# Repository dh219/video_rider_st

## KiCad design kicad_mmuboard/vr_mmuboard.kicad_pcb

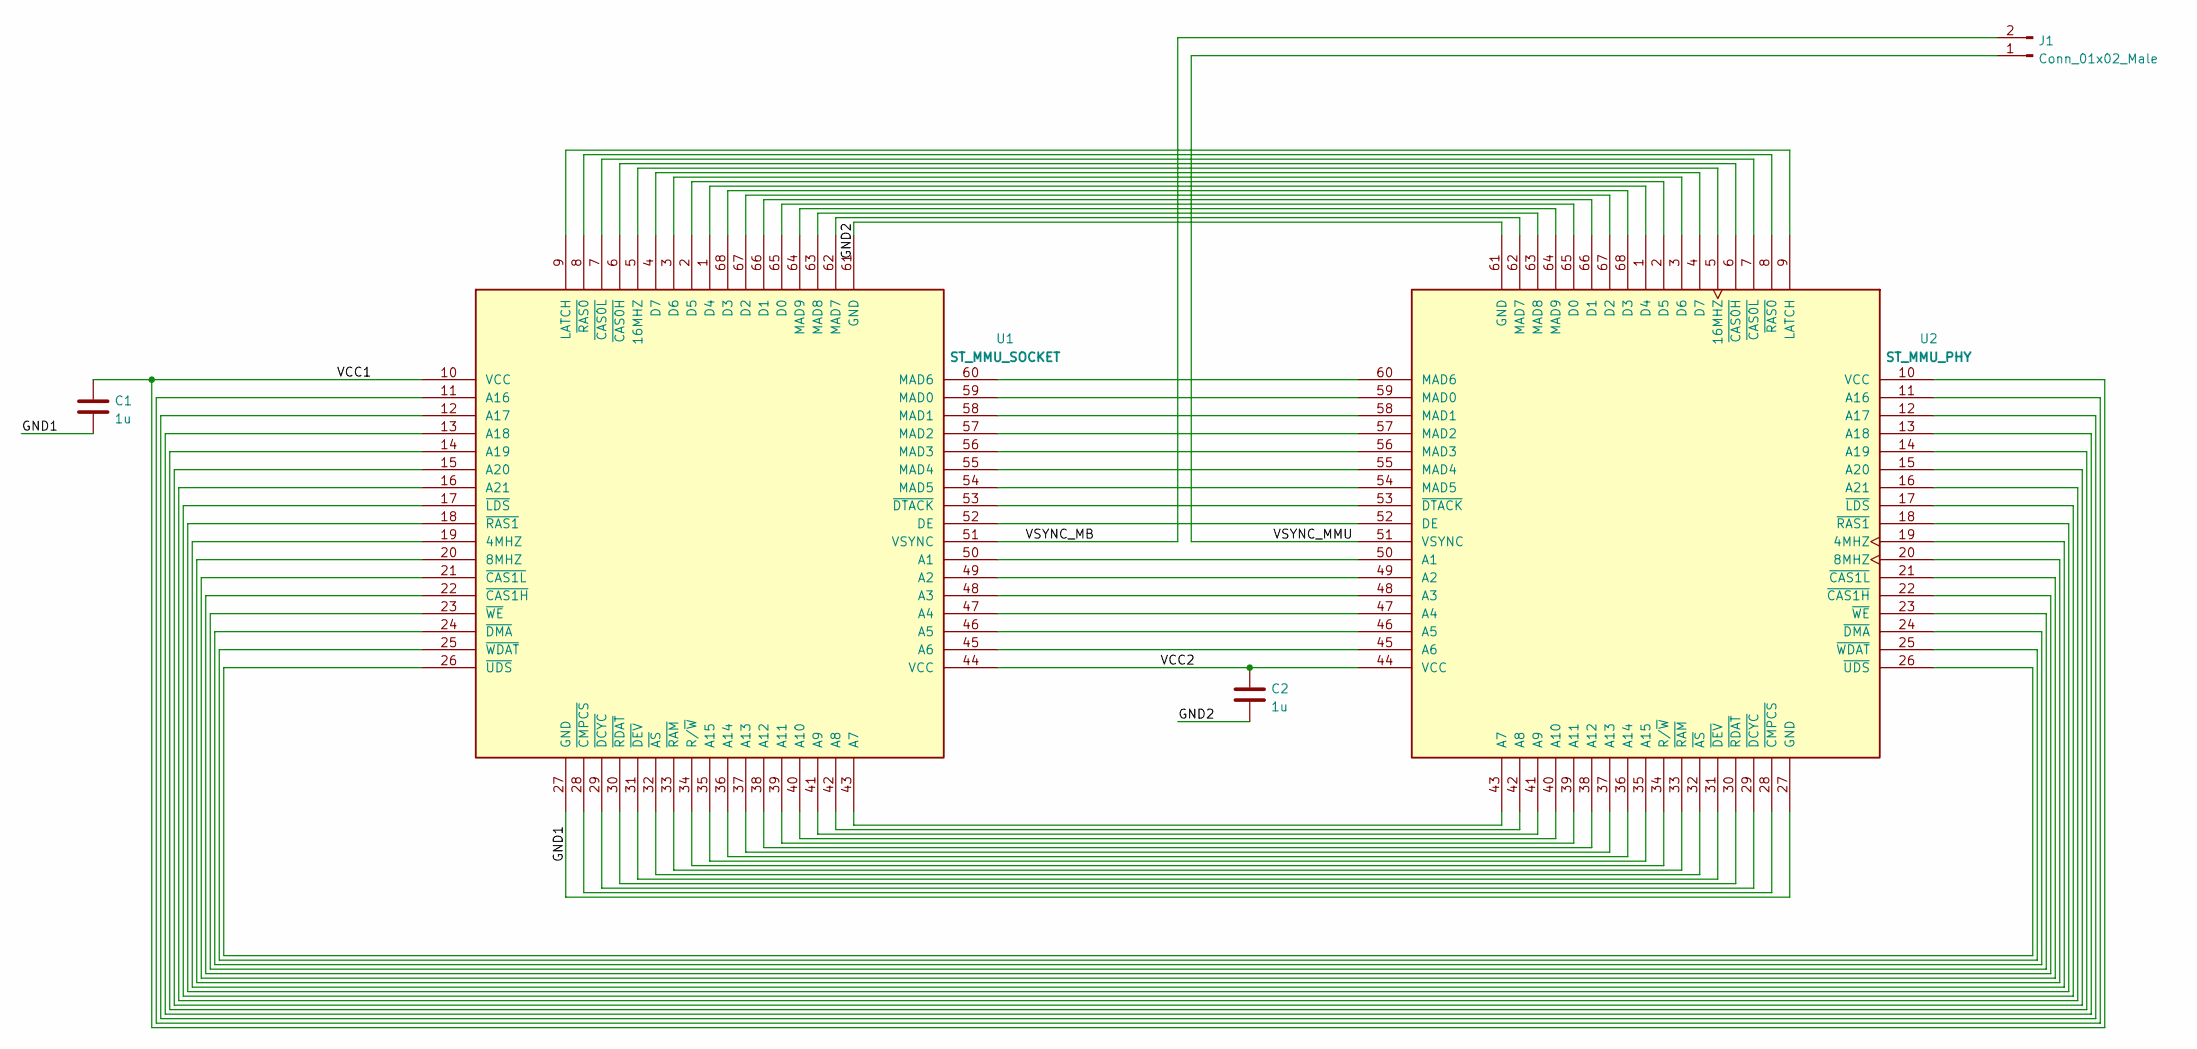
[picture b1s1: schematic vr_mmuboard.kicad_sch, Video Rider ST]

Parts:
C1, C2: 1u; C_0805_2012Metric_Pad1.18x1.45mm_HandSolder
J1: Conn_01x02_Male; PinHeader_1x02_P2.54mm_Horizontal
U1: ST_MMU_SOCKET; PLCC68_male_pins
U2: ST_MMU_PHY; PLCC-68_THT-Socket

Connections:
/GND1: C1.2, U1.27 (GND), U2.27 (GND)
/GND2: C2.2, U1.61 (GND), U2.61 (GND)
/VCC1: C1.1, U1.10 (VCC), U2.10 (VCC)
/VCC2: C2.1, U1.44 (VCC), U2.44 (VCC)
/VSYNC_MB: J1.2, U1.51 (VSYNC)
/VSYNC_MMU: J1.1, U2.51 (VSYNC)
unnamed: U1.1 (D4), U2.1 (D4)
unnamed: U1.2 (D5), U2.2 (D5)
unnamed: U1.3 (D6), U2.3 (D6)
unnamed: U1.4 (D7), U2.4 (D7)
unnamed: U1.5 (16MHZ), U2.5 (16MHZ)
unnamed: U1.6 (~CAS0H), U2.6 (~CAS0H)
unnamed: U1.7 (~CAS0L), U2.7 (~CAS0L)
unnamed: U1.8 (~RAS0), U2.8 (~RAS0)
unnamed: U1.9 (LATCH), U2.9 (LATCH)
unnamed: U1.11 (A16), U2.11 (A16)
unnamed: U1.12 (A17), U2.12 (A17)
unnamed: U1.13 (A18), U2.13 (A18)
unnamed: U1.14 (A19), U2.14 (A19)
unnamed: U1.15 (A20), U2.15 (A20)
unnamed: U1.16 (A21), U2.16 (A21)
unnamed: U1.17 (~LDS), U2.17 (~LDS)
unnamed: U1.18 (~RAS1), U2.18 (~RAS1)
unnamed: U1.19 (4MHZ), U2.19 (4MHZ)
unnamed: U1.20 (8MHZ), U2.20 (8MHZ)
unnamed: U1.21 (~CAS1L), U2.21 (~CAS1L)
unnamed: U1.22 (~CAS1H), U2.22 (~CAS1H)
unnamed: U1.23 (~WE), U2.23 (~WE)
unnamed: U1.24 (~DMA), U2.24 (~DMA)
unnamed: U1.25 (~WDAT), U2.25 (~WDAT)
unnamed: U1.26 (~UDS), U2.26 (~UDS)
unnamed: U1.28 (~CMPCS), U2.28 (~CMPCS)
unnamed: U1.29 (~DCYC), U2.29 (~DCYC)
unnamed: U1.30 (~RDAT), U2.30 (~RDAT)
unnamed: U1.31 (~DEV), U2.31 (~DEV)
unnamed: U1.32 (~AS), U2.32 (~AS)
unnamed: U1.33 (~RAM), U2.33 (~RAM)
unnamed: U1.34 (R/~W), U2.34 (R/~W)
unnamed: U1.35 (A15), U2.35 (A15)
unnamed: U1.36 (A14), U2.36 (A14)
unnamed: U1.37 (A13), U2.37 (A13)
unnamed: U1.38 (A12), U2.38 (A12)
unnamed: U1.39 (A11), U2.39 (A11)
unnamed: U1.40 (A10), U2.40 (A10)
unnamed: U1.41 (A9), U2.41 (A9)
unnamed: U1.42 (A8), U2.42 (A8)
unnamed: U1.43 (A7), U2.43 (A7)
unnamed: U1.45 (A6), U2.45 (A6)
unnamed: U1.46 (A5), U2.46 (A5)
unnamed: U1.47 (A4), U2.47 (A4)
unnamed: U1.48 (A3), U2.48 (A3)
unnamed: U1.49 (A2), U2.49 (A2)
unnamed: U1.50 (A1), U2.50 (A1)
unnamed: U1.52 (DE), U2.52 (DE)
unnamed: U1.53 (~DTACK), U2.53 (~DTACK)
unnamed: U1.54 (MAD5), U2.54 (MAD5)
unnamed: U1.55 (MAD4), U2.55 (MAD4)
unnamed: U1.56 (MAD3), U2.56 (MAD3)
unnamed: U1.57 (MAD2), U2.57 (MAD2)
unnamed: U1.58 (MAD1), U2.58 (MAD1)
unnamed: U1.59 (MAD0), U2.59 (MAD0)
unnamed: U1.60 (MAD6), U2.60 (MAD6)
unnamed: U1.62 (MAD7), U2.62 (MAD7)
unnamed: U1.63 (MAD8), U2.63 (MAD8)
unnamed: U1.64 (MAD9), U2.64 (MAD9)
unnamed: U1.65 (D0), U2.65 (D0)
unnamed: U1.66 (D1), U2.66 (D1)
unnamed: U1.67 (D2), U2.67 (D2)
unnamed: U1.68 (D3), U2.68 (D3)

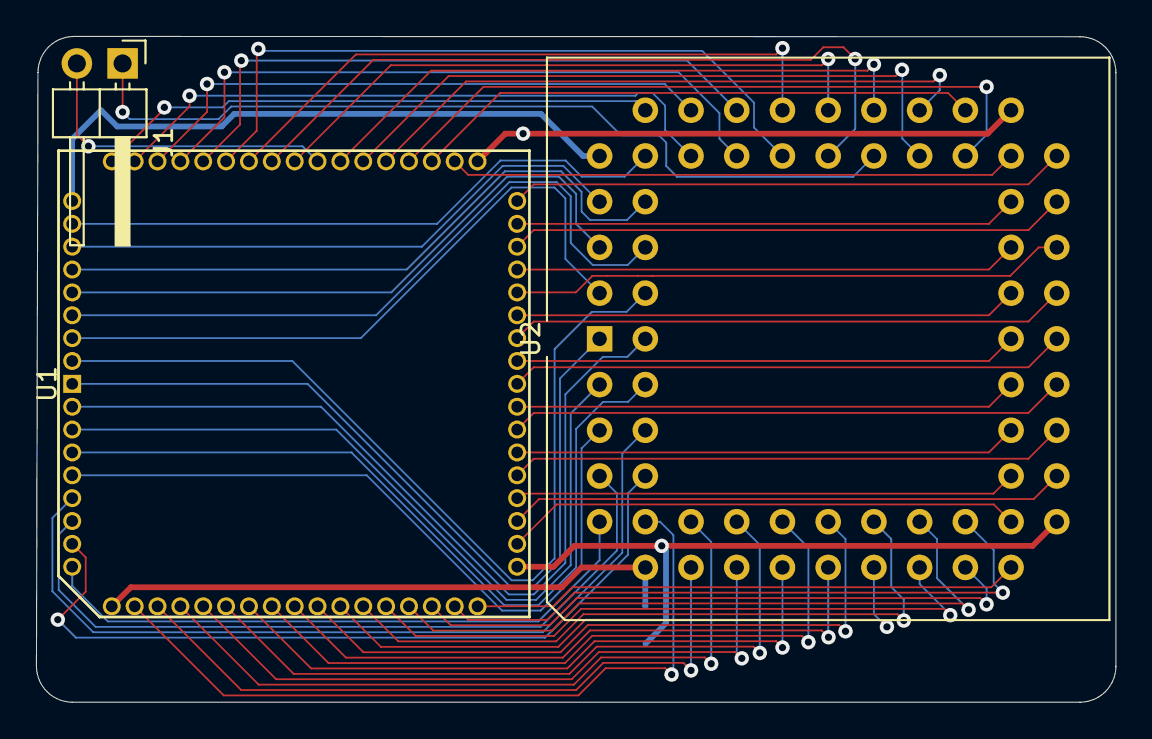
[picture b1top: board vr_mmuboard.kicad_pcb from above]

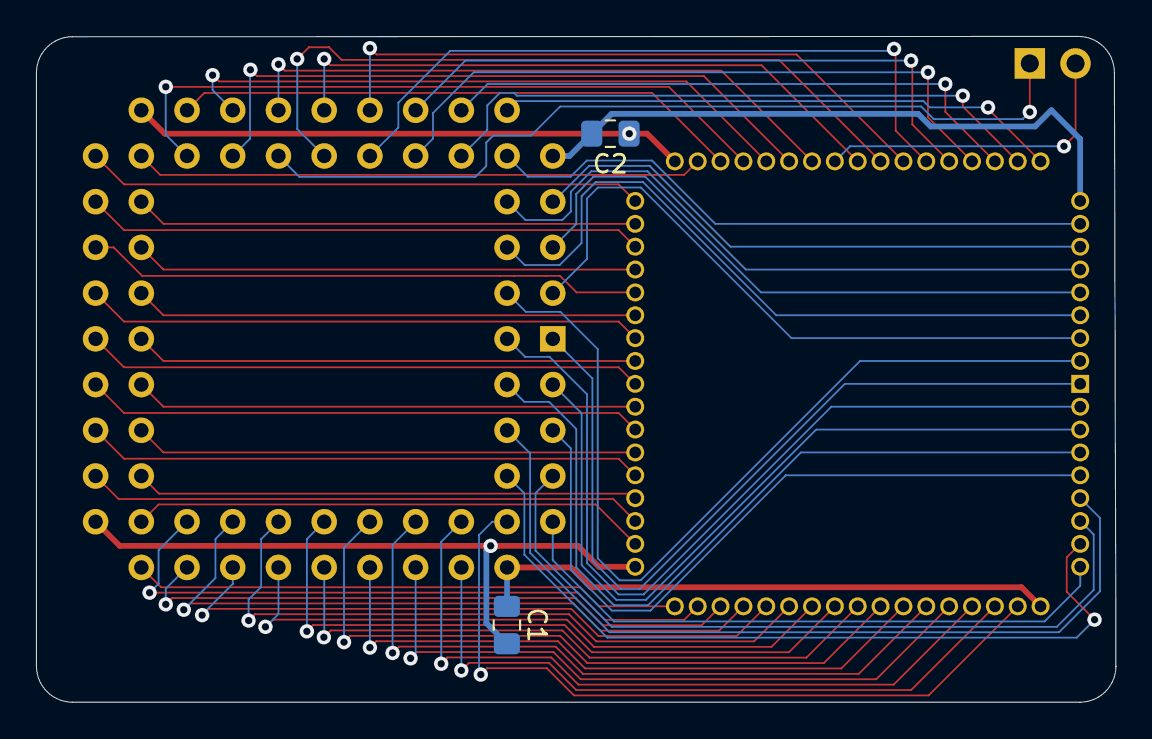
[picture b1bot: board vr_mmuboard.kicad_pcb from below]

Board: 2 copper layers, 60.0 x 37.0 mm, 5 parts (2 on the bottom side), 69 nets.

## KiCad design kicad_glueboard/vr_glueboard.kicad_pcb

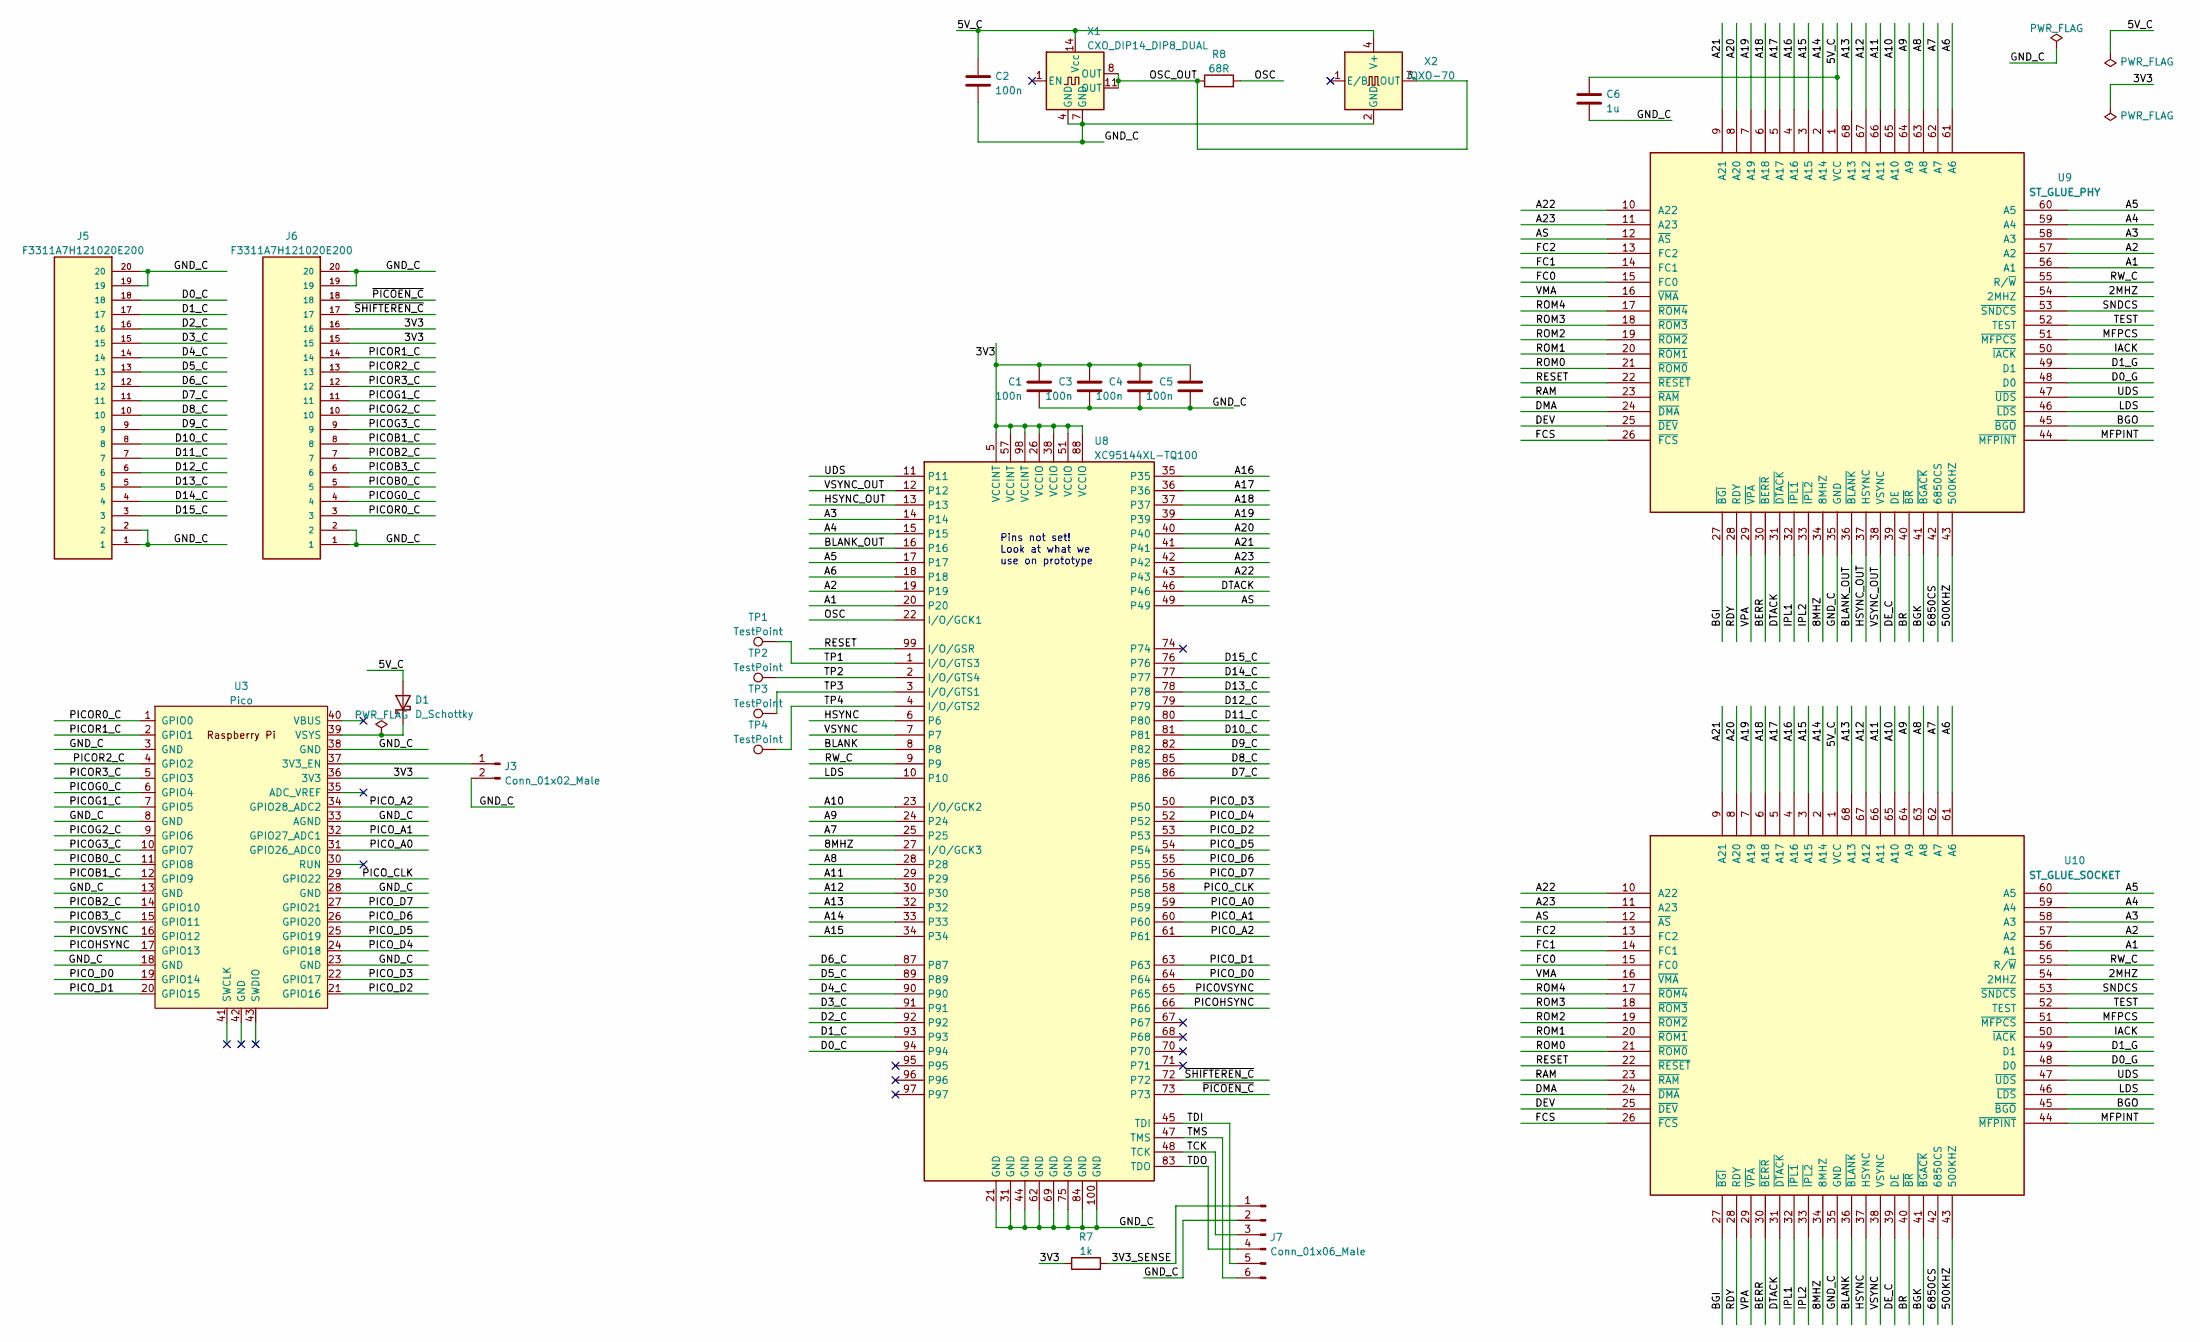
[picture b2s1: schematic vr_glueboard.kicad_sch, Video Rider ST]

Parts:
C1, C2, C3, C4, C5: 100n; C_0805_2012Metric_Pad1.18x1.45mm_HandSolder
C6: 1u; C_0805_2012Metric_Pad1.18x1.45mm_HandSolder
D1: D_Schottky; D_0805_2012Metric_Pad1.15x1.40mm_HandSolder
J3: Conn_01x02_Male; PinHeader_1x02_P2.54mm_Vertical
J5, J6: F3311A7H121020E200; AMPHENOL_F3311A7H121020E200; PARTREV A
J7: Conn_01x06_Male; PinHeader_1x06_P2.54mm_Vertical
R7: 1k; R_0805_2012Metric_Pad1.20x1.40mm_HandSolder
R8: 68R; R_0805_2012Metric_Pad1.20x1.40mm_HandSolder
TP1, TP2, TP3, TP4: TestPoint; TestPoint_THTPad_1.5x1.5mm_Drill0.7mm
U3: Pico; RPi_Pico_SMD_TH
U8: XC95144XL-TQ100; TQFP-100_14x14mm_P0.5mm
U9: ST_GLUE_PHY; PLCC68_male_pins
U10: ST_GLUE_SOCKET; PLCC-68_THT-Socket
X1: CXO_DIP14_DIP8_DUAL; CXO_Dual_DIP
X2: IQXO-70; Oscillator_SMD_IQD_IQXO70-4Pin_7.5x5.0mm

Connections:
/2MHZ: U9.54 (2MHZ), U10.54 (2MHZ)
/3V3: C1.1, C3.1, C4.1, C5.1, J6.15, J6.16, R7.1, U3.36 (3V3), U8.5 (VCCINT), U8.26 (VCCIO), U8.38 (VCCIO), U8.51 (VCCIO), U8.57 (VCCINT), U8.88 (VCCIO), U8.98 (VCCINT)
/3V3_SENSE: J7.1, R7.2
/5V_C: C2.1, C6.1, D1.2 (A), U9.1 (VCC), U10.1 (VCC), X1.14 (Vcc), X2.4 (V+)
/8MHZ: U8.27 (I/O/GCK3), U9.34 (8MHZ), U10.34 (8MHZ)
/500KHZ: U9.43 (500KHZ), U10.43 (500KHZ)
/6850CS: U9.42 (6850CS), U10.42 (6850CS)
/A1: U8.20, U9.56 (A1), U10.56 (A1)
/A2: U8.19, U9.57 (A2), U10.57 (A2)
/A3: U8.14, U9.58 (A3), U10.58 (A3)
/A4: U8.15, U9.59 (A4), U10.59 (A4)
/A5: U8.17, U9.60 (A5), U10.60 (A5)
/A6: U8.18, U9.61 (A6), U10.61 (A6)
/A7: U8.25, U9.62 (A7), U10.62 (A7)
/A8: U8.28, U9.63 (A8), U10.63 (A8)
/A9: U8.24, U9.64 (A9), U10.64 (A9)
/A10: U8.23 (I/O/GCK2), U9.65 (A10), U10.65 (A10)
/A11: U8.29, U9.66 (A11), U10.66 (A11)
/A12: U8.30, U9.67 (A12), U10.67 (A12)
/A13: U8.32, U9.68 (A13), U10.68 (A13)
/A14: U8.33, U9.2 (A14), U10.2 (A14)
/A15: U8.34, U9.3 (A15), U10.3 (A15)
/A16: U8.35, U9.4 (A16), U10.4 (A16)
/A17: U8.36, U9.5 (A17), U10.5 (A17)
/A18: U8.37, U9.6 (A18), U10.6 (A18)
/A19: U8.39, U9.7 (A19), U10.7 (A19)
/A20: U8.40, U9.8 (A20), U10.8 (A20)
/A21: U8.41, U9.9 (A21), U10.9 (A21)
/A22: U8.43, U9.10 (A22), U10.10 (A22)
/A23: U8.42, U9.11 (A23), U10.11 (A23)
/AS: U8.49, U9.12 (~AS), U10.12 (~AS)
/BERR: U9.30 (~BERR), U10.30 (~BERR)
/BGI: U9.27 (~BGI), U10.27 (~BGI)
/BGK: U9.41 (~BGACK), U10.41 (~BGACK)
/BGO: U9.45 (~BGO), U10.45 (~BGO)
/BLANK: U8.8, U10.36 (~BLANK)
/BLANK_OUT: U8.16, U9.36 (~BLANK)
/BR: U9.40 (~BR), U10.40 (~BR)
/D0_C: J5.18, U8.94
/D0_G: U9.48 (D0), U10.48 (D0)
/D1_C: J5.17, U8.93
/D1_G: U9.49 (D1), U10.49 (D1)
/D2_C: J5.16, U8.92
/D3_C: J5.15, U8.91
/D4_C: J5.14, U8.90
/D5_C: J5.13, U8.89
/D6_C: J5.12, U8.87
/D7_C: J5.11, U8.86
/D8_C: J5.10, U8.85
/D9_C: J5.9, U8.82
/D10_C: J5.8, U8.81
/D11_C: J5.7, U8.80
/D12_C: J5.6, U8.79
/D13_C: J5.5, U8.78
/D14_C: J5.4, U8.77
/D15_C: J5.3, U8.76
/DEV: U9.25 (~DEV), U10.25 (~DEV)
/DE_C: U9.39 (DE), U10.39 (DE)
/DMA: U9.24 (~DMA), U10.24 (~DMA)
/DTACK: U8.46, U9.31 (~DTACK), U10.31 (~DTACK)
/FC0: U9.15 (FC0), U10.15 (FC0)
/FC1: U9.14 (FC1), U10.14 (FC1)
/FC2: U9.13 (FC2), U10.13 (FC2)
/FCS: U9.26 (~FCS), U10.26 (~FCS)
/GND_C: C1.2, C2.2, C3.2, C4.2, C5.2, C6.2, J3.2, J5.1, J5.2, J5.19, J5.20, J5.SH1, J5.SH2, J6.1, J6.2, J6.19, J6.20, J6.SH1, J6.SH2, J7.2, U3.3 (GND), U3.8 (GND), U3.13 (GND), U3.18 (GND), U3.23 (GND), U3.28 (GND), U3.33 (AGND), U3.38 (GND), U8.21 (GND), U8.31 (GND), U8.44 (GND), U8.62 (GND), U8.69 (GND), U8.75 (GND), U8.84 (GND), U8.100 (GND), U9.35 (GND), U10.35 (GND), X1.4 (GND), X1.7 (GND), X2.2 (GND)
/HSYNC: U8.6, U10.37 (HSYNC)
/HSYNC_OUT: U8.13, U9.37 (HSYNC)
/IACK: U9.50 (~IACK), U10.50 (~IACK)
/IPL1: U9.32 (~IPL1), U10.32 (~IPL1)
/IPL2: U9.33 (~IPL2), U10.33 (~IPL2)
/LDS: U8.10, U9.46 (~LDS), U10.46 (~LDS)
/MFPCS: U9.51 (~MFPCS), U10.51 (~MFPCS)
/MFPINT: U9.44 (~MFPINT), U10.44 (~MFPINT)
/OSC: R8.2, U8.22 (I/O/GCK1)
/OSC_OUT: R8.1, X1.8 (OUT), X1.11 (OUT), X2.3 (OUT)
/PICOB0_C: J6.5, U3.11 (GPIO8)
/PICOB1_C: J6.8, U3.12 (GPIO9)
/PICOB2_C: J6.7, U3.14 (GPIO10)
/PICOB3_C: J6.6, U3.15 (GPIO11)
/PICOG0_C: J6.4, U3.6 (GPIO4)
/PICOG1_C: J6.11, U3.7 (GPIO5)
/PICOG2_C: J6.10, U3.9 (GPIO6)
/PICOG3_C: J6.9, U3.10 (GPIO7)
/PICOHSYNC: U3.17 (GPIO13), U8.66
/PICOR0_C: J6.3, U3.1 (GPIO0)
/PICOR1_C: J6.14, U3.2 (GPIO1)
/PICOR2_C: J6.13, U3.4 (GPIO2)
/PICOR3_C: J6.12, U3.5 (GPIO3)
/PICOVSYNC: U3.16 (GPIO12), U8.65
/PICO_A0: U3.31 (GPIO26_ADC0), U8.59
/PICO_A1: U3.32 (GPIO27_ADC1), U8.60
/PICO_A2: U3.34 (GPIO28_ADC2), U8.61
/PICO_CLK: U3.29 (GPIO22), U8.58
/PICO_D0: U3.19 (GPIO14), U8.64
/PICO_D1: U3.20 (GPIO15), U8.63
/PICO_D2: U3.21 (GPIO16), U8.53
/PICO_D3: U3.22 (GPIO17), U8.50
/PICO_D4: U3.24 (GPIO18), U8.52
/PICO_D5: U3.25 (GPIO19), U8.54
/PICO_D6: U3.26 (GPIO20), U8.55
/PICO_D7: U3.27 (GPIO21), U8.56
/RAM: U9.23 (~RAM), U10.23 (~RAM)
/RDY: U9.28 (RDY), U10.28 (RDY)
/RESET: U8.99 (I/O/GSR), U9.22 (~RESET), U10.22 (~RESET)
/ROM0: U9.21 (~ROM0), U10.21 (~ROM0)
/ROM1: U9.20 (~ROM1), U10.20 (~ROM1)
/ROM2: U9.19 (~ROM2), U10.19 (~ROM2)
/ROM3: U9.18 (~ROM3), U10.18 (~ROM3)
/ROM4: U9.17 (~ROM4), U10.17 (~ROM4)
/RW_C: U8.9, U9.55 (R/~W), U10.55 (R/~W)
/SNDCS: U9.53 (~SNDCS), U10.53 (~SNDCS)
/TCK: J7.3, U8.48 (TCK)
/TDI: J7.5, U8.45 (TDI)
/TDO: J7.4, U8.83 (TDO)
/TEST: U9.52 (TEST), U10.52 (TEST)
/TMS: J7.6, U8.47 (TMS)
/TP1: TP1.1, U8.1 (I/O/GTS3)
/TP2: TP2.1, U8.2 (I/O/GTS4)
/TP3: TP3.1, U8.3 (I/O/GTS1)
/TP4: TP4.1, U8.4 (I/O/GTS2)
/UDS: U8.11, U9.47 (~UDS), U10.47 (~UDS)
/VMA: U9.16 (~VMA), U10.16 (~VMA)
/VPA: U9.29 (~VPA), U10.29 (~VPA)
/VSYNC: U8.7, U10.38 (VSYNC)
/VSYNC_OUT: U8.12, U9.38 (VSYNC)
/~PICOEN_C: J6.18, U8.73
/~SHIFTEREN_C: J6.17, U8.72
unnamed: D1.1 (K), U3.39 (VSYS)
unnamed: J3.1, U3.37 (3V3_EN)

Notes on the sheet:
Pins not set! Look at what we use on prototype

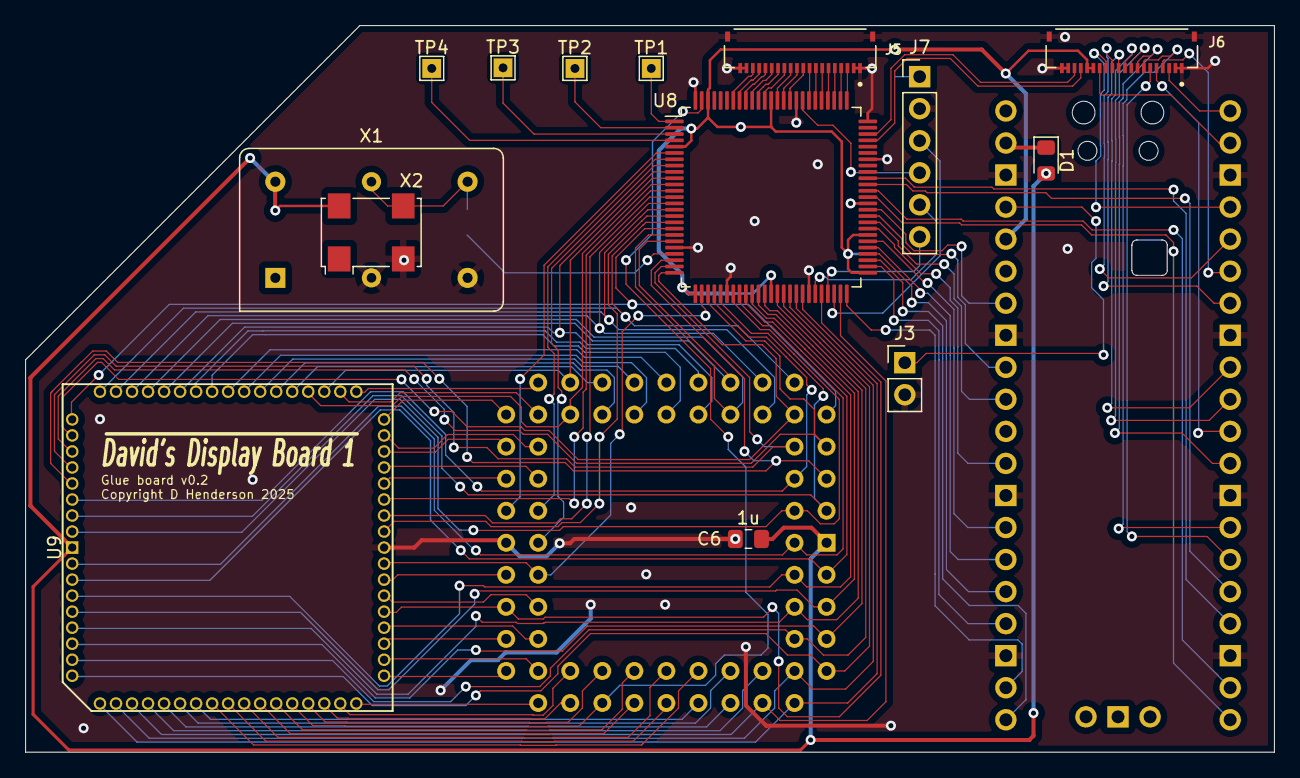
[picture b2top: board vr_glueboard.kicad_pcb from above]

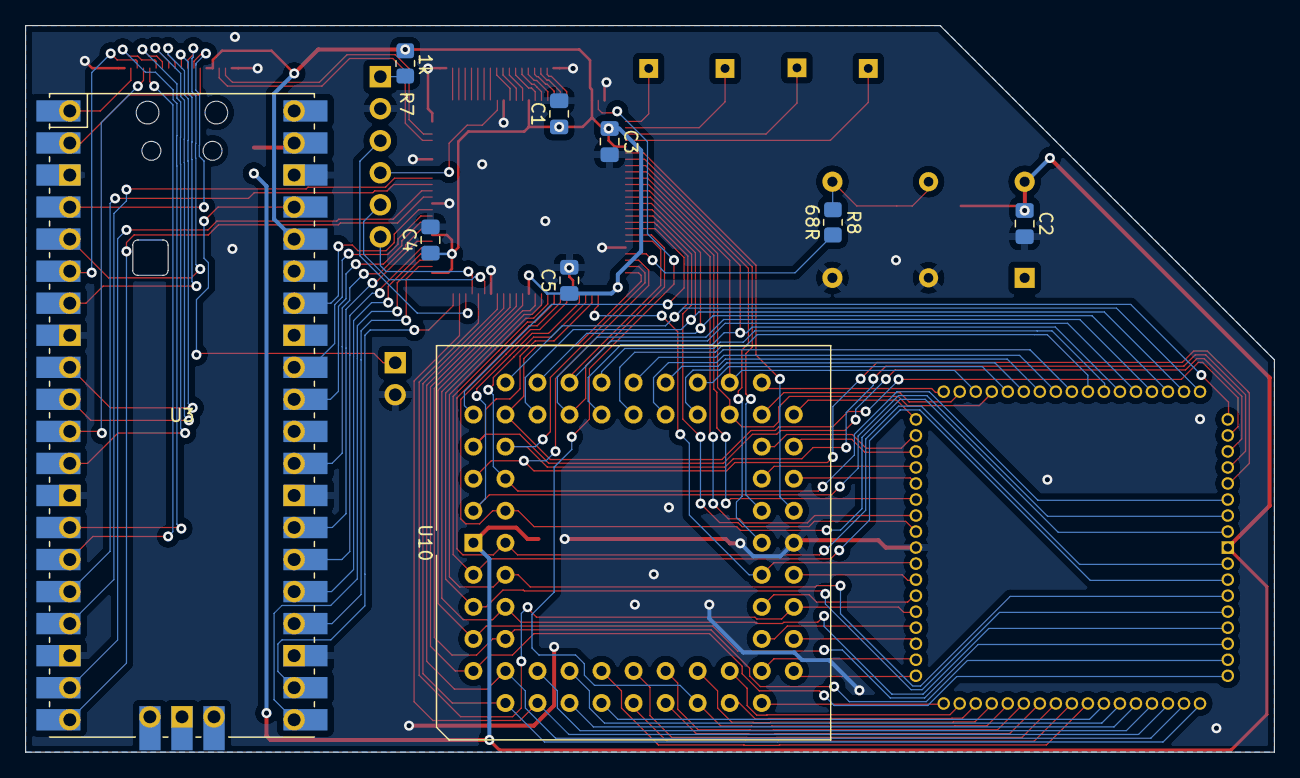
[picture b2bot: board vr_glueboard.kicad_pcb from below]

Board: 2 copper layers, 99.0 x 57.6 mm, 23 parts (9 on the bottom side), 129 nets.

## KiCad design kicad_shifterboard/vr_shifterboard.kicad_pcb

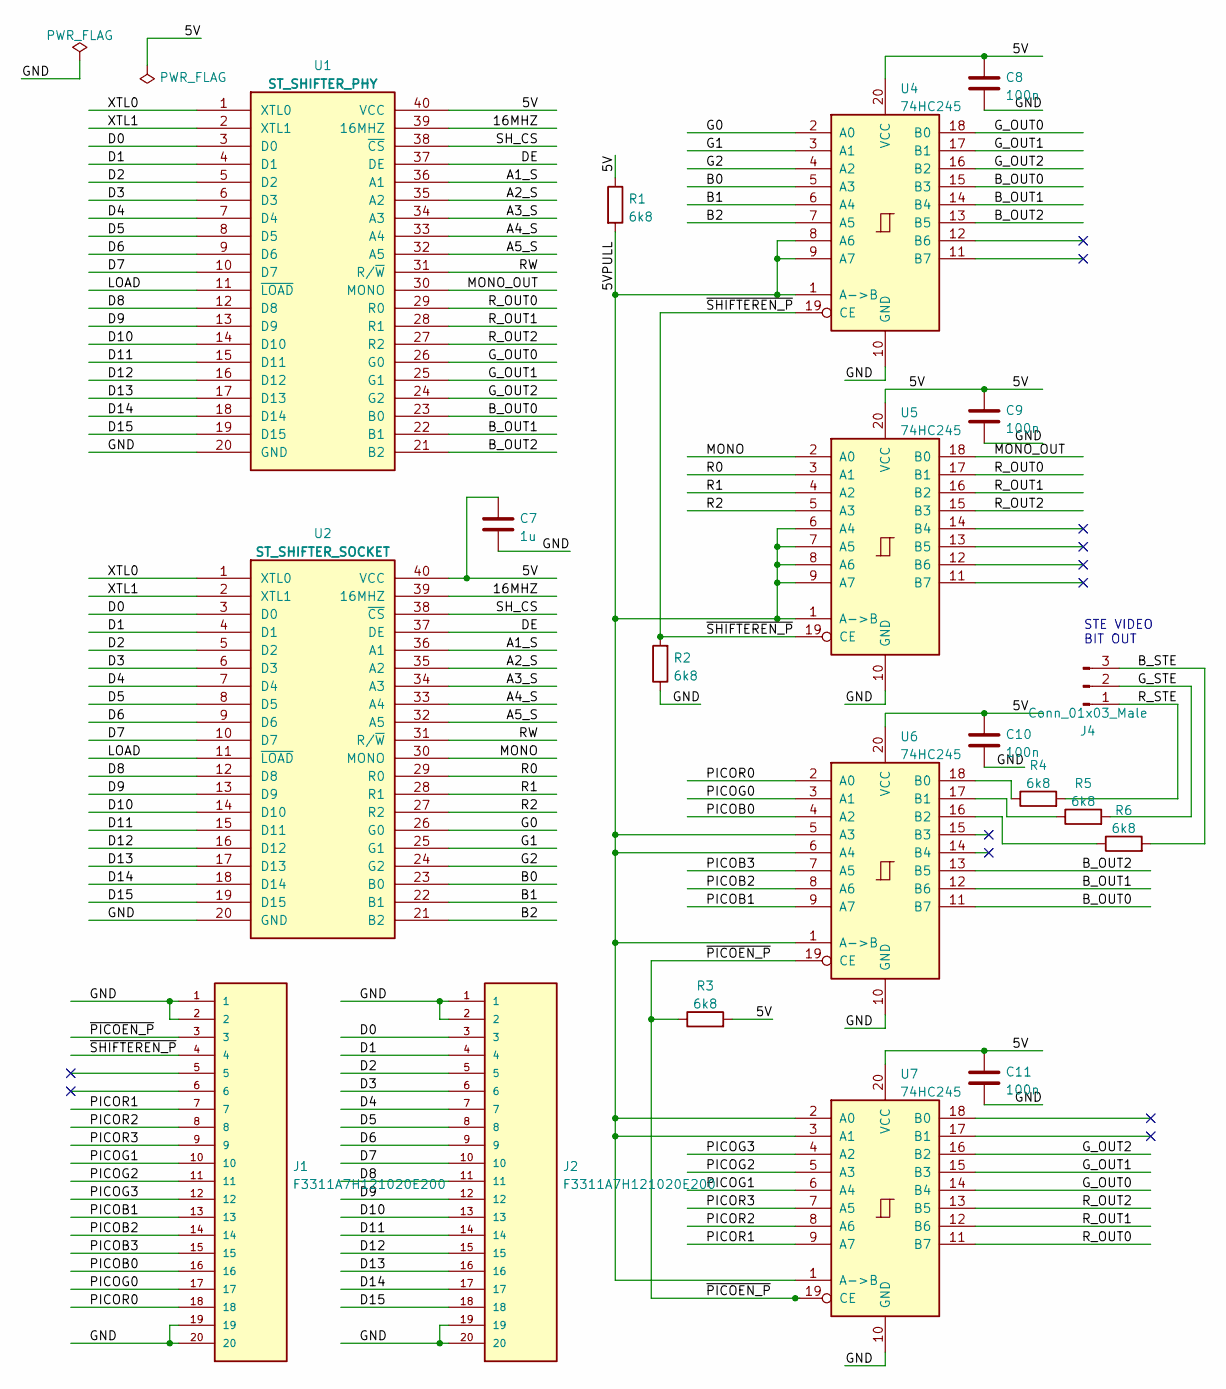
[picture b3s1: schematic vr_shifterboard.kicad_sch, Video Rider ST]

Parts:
C7: 1u; C_0805_2012Metric_Pad1.18x1.45mm_HandSolder
C8, C9, C10, C11: 100n; C_0805_2012Metric_Pad1.18x1.45mm_HandSolder
J1, J2: F3311A7H121020E200; AMPHENOL_F3311A7H121020E200; PARTREV A
J4: Conn_01x03_Male; PinHeader_1x03_P2.54mm_Vertical
R1, R2, R3, R4, R5, R6: 6k8; R_0805_2012Metric_Pad1.20x1.40mm_HandSolder
U1: ST_SHIFTER_PHY; DIP-40_W15.24mm_LongPads
U2: ST_SHIFTER_SOCKET; DIP-40_W15.24mm_LongPads
U4, U5, U6, U7: 74HC245; TSSOP-20_4.4x6.5mm_P0.65mm

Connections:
/5V: C7.1, C8.1, C9.1, C10.1, C11.1, R1.1, R3.2, U1.40 (VCC), U2.40 (VCC), U4.20 (VCC), U5.20 (VCC), U6.20 (VCC), U7.20 (VCC)
/5VPULL: R1.2, U4.1 (A->B), U4.8 (A6), U4.9 (A7), U5.1 (A->B), U5.6 (A4), U5.7 (A5), U5.8 (A6), U5.9 (A7), U6.1 (A->B), U6.5 (A3), U6.6 (A4), U7.1 (A->B), U7.2 (A0), U7.3 (A1)
/16MHZ: U1.39 (16MHZ), U2.39 (16MHZ)
/A1_S: U1.36 (A1), U2.36 (A1)
/A2_S: U1.35 (A2), U2.35 (A2)
/A3_S: U1.34 (A3), U2.34 (A3)
/A4_S: U1.33 (A4), U2.33 (A4)
/A5_S: U1.32 (A5), U2.32 (A5)
/B0: U2.23 (B0), U4.5 (A3)
/B1: U2.22 (B1), U4.6 (A4)
/B2: U2.21 (B2), U4.7 (A5)
/B_OUT0: U1.23 (B0), U4.15 (B3), U6.11 (B7)
/B_OUT1: U1.22 (B1), U4.14 (B4), U6.12 (B6)
/B_OUT2: U1.21 (B2), U4.13 (B5), U6.13 (B5)
/B_STE: J4.3, R6.2
/D0: J2.3, U1.3 (D0), U2.3 (D0)
/D1: J2.4, U1.4 (D1), U2.4 (D1)
/D2: J2.5, U1.5 (D2), U2.5 (D2)
/D3: J2.6, U1.6 (D3), U2.6 (D3)
/D4: J2.7, U1.7 (D4), U2.7 (D4)
/D5: J2.8, U1.8 (D5), U2.8 (D5)
/D6: J2.9, U1.9 (D6), U2.9 (D6)
/D7: J2.10, U1.10 (D7), U2.10 (D7)
/D8: J2.11, U1.12 (D8), U2.12 (D8)
/D9: J2.12, U1.13 (D9), U2.13 (D9)
/D10: J2.13, U1.14 (D10), U2.14 (D10)
/D11: J2.14, U1.15 (D11), U2.15 (D11)
/D12: J2.15, U1.16 (D12), U2.16 (D12)
/D13: J2.16, U1.17 (D13), U2.17 (D13)
/D14: J2.17, U1.18 (D14), U2.18 (D14)
/D15: J2.18, U1.19 (D15), U2.19 (D15)
/DE: U1.37 (DE), U2.37 (DE)
/G0: U2.26 (G0), U4.2 (A0)
/G1: U2.25 (G1), U4.3 (A1)
/G2: U2.24 (G2), U4.4 (A2)
/GND: C7.2, C8.2, C9.2, C10.2, C11.2, J1.1, J1.2, J1.19, J1.20, J1.SH1, J1.SH2, J2.1, J2.2, J2.19, J2.20, J2.SH1, J2.SH2, R2.1, U1.20 (GND), U2.20 (GND), U4.10 (GND), U5.10 (GND), U6.10 (GND), U7.10 (GND)
/G_OUT0: U1.26 (G0), U4.18 (B0), U7.14 (B4)
/G_OUT1: U1.25 (G1), U4.17 (B1), U7.15 (B3)
/G_OUT2: U1.24 (G2), U4.16 (B2), U7.16 (B2)
/G_STE: J4.2, R5.2
/LOAD: U1.11 (~LOAD), U2.11 (~LOAD)
/MONO: U2.30 (MONO), U5.2 (A0)
/MONO_OUT: U1.30 (MONO), U5.18 (B0)
/PICOB0: J1.16, U6.4 (A2)
/PICOB1: J1.13, U6.9 (A7)
/PICOB2: J1.14, U6.8 (A6)
/PICOB3: J1.15, U6.7 (A5)
/PICOG0: J1.17, U6.3 (A1)
/PICOG1: J1.10, U7.6 (A4)
/PICOG2: J1.11, U7.5 (A3)
/PICOG3: J1.12, U7.4 (A2)
/PICOR0: J1.18, U6.2 (A0)
/PICOR1: J1.7, U7.9 (A7)
/PICOR2: J1.8, U7.8 (A6)
/PICOR3: J1.9, U7.7 (A5)
/R0: U2.29 (R0), U5.3 (A1)
/R1: U2.28 (R1), U5.4 (A2)
/R2: U2.27 (R2), U5.5 (A3)
/RW: U1.31 (R/~W), U2.31 (R/~W)
/R_OUT0: U1.29 (R0), U5.17 (B1), U7.11 (B7)
/R_OUT1: U1.28 (R1), U5.16 (B2), U7.12 (B6)
/R_OUT2: U1.27 (R2), U5.15 (B3), U7.13 (B5)
/R_STE: J4.1, R4.2
/SH_CS: U1.38 (~CS), U2.38 (~CS)
/XTL0: U1.1 (XTL0), U2.1 (XTL0)
/XTL1: U1.2 (XTL1), U2.2 (XTL1)
/~PICOEN_P: J1.3, R3.1, U6.19 (CE), U7.19 (CE)
/~SHIFTEREN_P: J1.4, R2.2, U4.19 (CE), U5.19 (CE)
unnamed: R4.1, U6.18 (B0)
unnamed: R5.1, U6.17 (B1)
unnamed: R6.1, U6.16 (B2)

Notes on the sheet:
STE VIDEO BIT OUT

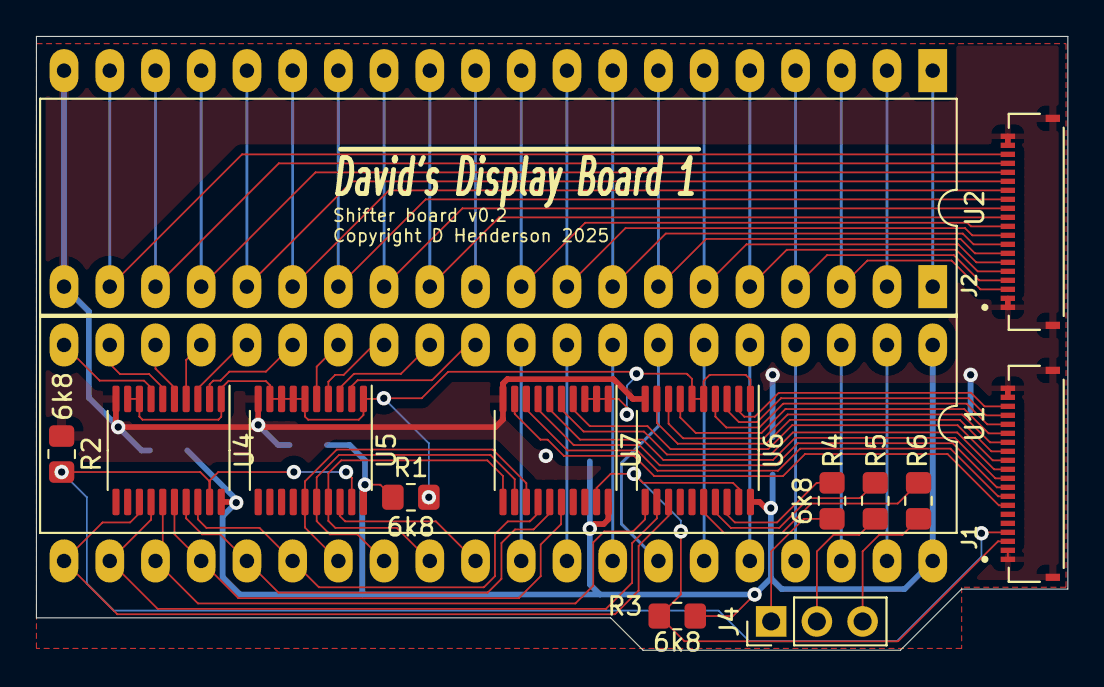
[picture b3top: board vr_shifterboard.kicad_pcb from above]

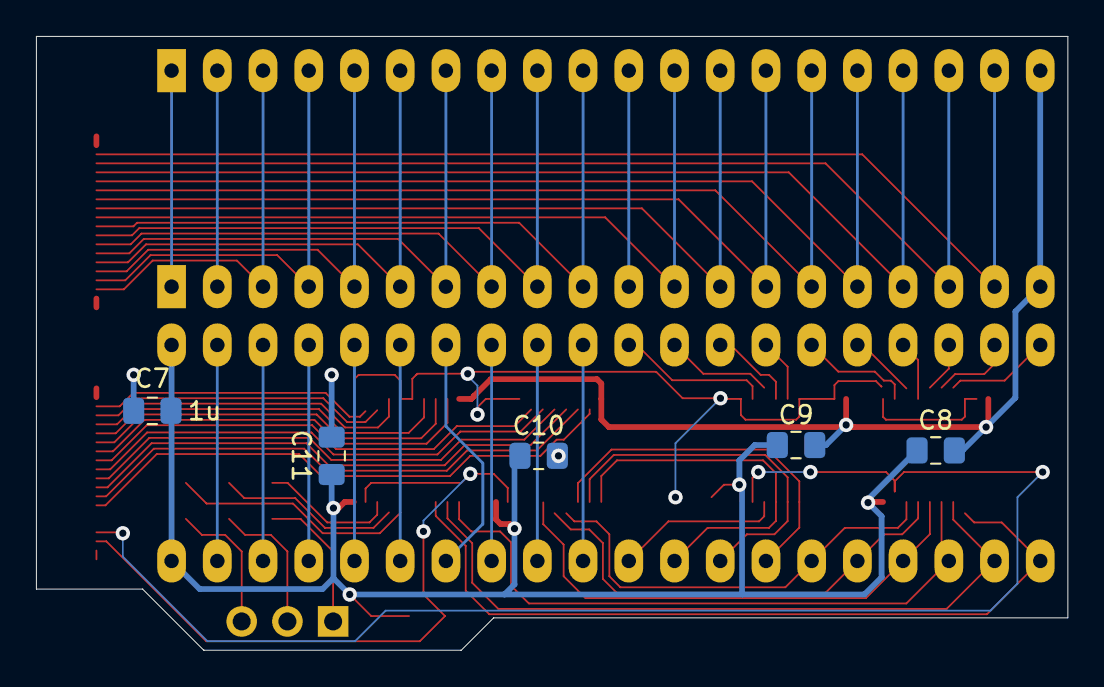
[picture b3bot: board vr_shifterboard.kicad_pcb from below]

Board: 2 copper layers, 57.3 x 34.1 mm, 20 parts (5 on the bottom side), 71 nets.

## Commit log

2023-10-26 Initial setup of the kicad files
2025-02-20 Most basic components now on schematic.
2025-02-20 Adding libs and initial draft of schematic complete
2025-02-21 Experimenting with board layout
2025-02-21 Adding connector library (F331) and kicad_pcb
2025-02-21 More layout experimentation
2025-02-23 Preliminary routeing of shifter board nearly complete
2025-02-25 Basic board outline and routeing done. Need sanity and DRC check
2025-02-25 Adding PLCC Plugs lib
2025-02-25 Rerouteing pico to bottom layer
2025-02-26 Adding support for other oscillators
2025-02-26 Just about ready to order, but need to check the dual dip library.
2025-02-27 Modified to single board as PCBWay increased the price by 9x!
2025-02-27 Hiding certain things from the BOM
2025-03-13 Passing DRC with corrected PLCC orientation.
2025-03-13 Adding split-out shifter board
2025-03-13 Split the shifter and glue boards into separate projects. Both passing DRC.
2025-03-13 Removing old kicad dir
2025-03-13 Preparing gerbers again
2025-03-14 A few mods to to the glueboard to ensure trace/edge cut separation and just some tiding up. Changed pico data pin order to get a better ground.
2025-07-10 Adding a new experimental mmuboard
2025-07-16 MMUBoard added to repo

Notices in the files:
kicad_glueboard/vr_glueboard.kicad_pcb:
Copyright D Henderson 2025
kicad_glueboard/vr_glueboard.kicad_sch:
Copyright 2025
Released under the terms of the GPLv2
